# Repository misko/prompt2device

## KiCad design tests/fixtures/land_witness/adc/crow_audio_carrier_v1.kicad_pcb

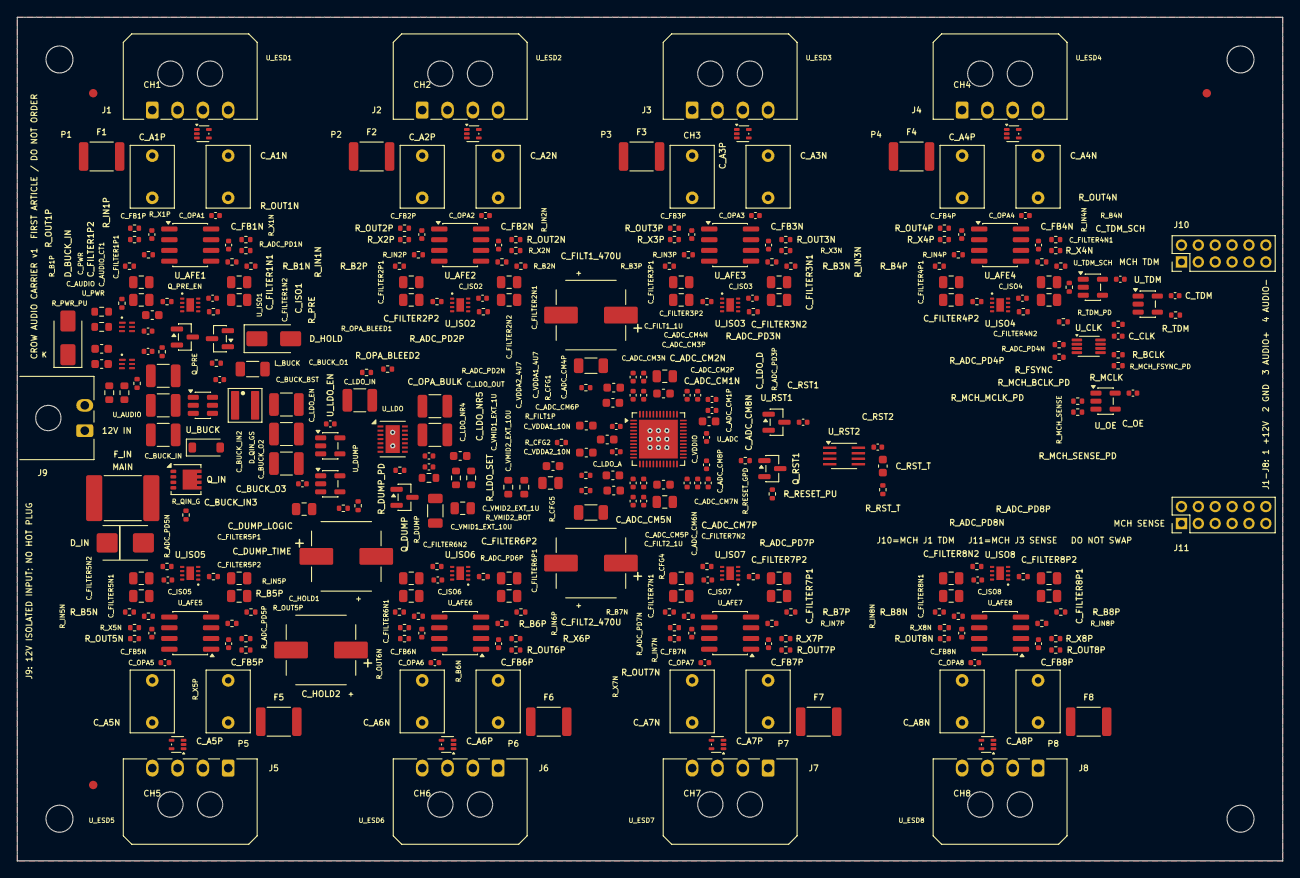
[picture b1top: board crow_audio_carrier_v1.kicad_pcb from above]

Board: 4 copper layers, 150.0 x 100.0 mm, 340 parts (0 on the bottom side), 178 nets, no tracks yet.

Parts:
C_A1N, C_A1P, C_A2N, C_A2P, C_A3N, C_A3P, C_A4N, C_A4P, C_A5N, C_A5P, C_A6N, C_A6P, C_A7N, C_A7P, C_A8N, C_A8P: 1uF; C_Rect_L7.2mm_W5.0mm_P5.00mm
C_ADC_CM1N, C_ADC_CM1P, C_ADC_CM2N, C_ADC_CM2P, C_ADC_CM3N, C_ADC_CM3P, C_ADC_CM4N, C_ADC_CM4P, C_ADC_CM5N, C_ADC_CM5P, C_ADC_CM6N, C_ADC_CM6P, C_ADC_CM7N, C_ADC_CM7P, C_ADC_CM8N, C_ADC_CM8P: 1nF; C_0402_1005Metric
C_AUDIO: 100nF; C_0402_1005Metric
C_AUDIO_CT1, C_AUDIO_CT2: 1uF; C_0603_1608Metric
C_BUCK_BST: 100nF; C_0402_1005Metric
C_BUCK_IN, C_BUCK_IN2, C_BUCK_IN3: 10uF; C_1210_3225Metric
C_BUCK_O1, C_BUCK_O2, C_BUCK_O3: 47uF; C_1210_3225Metric
C_CLK: 100nF; C_0402_1005Metric
C_DUMP_LOGIC: 100nF; C_0402_1005Metric
C_DUMP_TIME: 15nF; C_0805_2012Metric
C_FB1N, C_FB1P, C_FB2N, C_FB2P, C_FB3N, C_FB3P, C_FB4N, C_FB4P, C_FB5N, C_FB5P, C_FB6N, C_FB6P, C_FB7N, C_FB7P, C_FB8N, C_FB8P: 680pF; C_0402_1005Metric
C_FILT1_1U, C_FILT2_1U: 1uF; C_0603_1608Metric
C_FILT1_10U, C_FILT2_10U: 10uF; C_0805_2012Metric
C_FILT1_470U, C_FILT2_470U: 470uF; Panasonic_EEEFK1A471P_8x10.2_Exact
C_FILTER1N1, C_FILTER1N2, C_FILTER1P1, C_FILTER1P2, C_FILTER2N1, C_FILTER2N2, C_FILTER2P1, C_FILTER2P2, C_FILTER3N1, C_FILTER3N2, C_FILTER3P1, C_FILTER3P2, C_FILTER4N1, C_FILTER4N2, C_FILTER4P1, C_FILTER4P2, C_FILTER5N1, C_FILTER5N2, C_FILTER5P1, C_FILTER5P2, C_FILTER6N1, C_FILTER6N2, C_FILTER6P1, C_FILTER6P2, C_FILTER7N1, C_FILTER7N2, C_FILTER7P1, C_FILTER7P2, C_FILTER8N1, C_FILTER8N2, C_FILTER8P1, C_FILTER8P2: 15nF; C_0805_2012Metric
C_HOLD1, C_HOLD2: 470uF; Panasonic_EEEFK1A471P_8x10.2_Exact
C_ISO1, C_ISO2, C_ISO3, C_ISO4, C_ISO5, C_ISO6, C_ISO7, C_ISO8: 100nF; C_0402_1005Metric
C_LDO_A: 4.7uF; C_0603_1608Metric
C_LDO_D: 4.7uF; C_0603_1608Metric
C_LDO_EN: 100nF; C_0402_1005Metric
C_LDO_IN: 47uF; C_1210_3225Metric
C_LDO_NR4, C_LDO_NR5: 1nF; C_0402_1005Metric
C_LDO_OUT: 47uF; C_1210_3225Metric
C_OE: 100nF; C_0402_1005Metric
C_OPA1, C_OPA2, C_OPA3, C_OPA4, C_OPA5, C_OPA6, C_OPA7, C_OPA8: 100nF; C_0402_1005Metric
C_OPA_BULK: 47uF; C_1210_3225Metric
C_PWR: 100nF; C_0402_1005Metric
C_PWR_CT: 1uF; C_0603_1608Metric
C_RST1, C_RST2: 100nF; C_0402_1005Metric
C_RST_T: 220nF; C_0603_1608Metric
C_TDM: 100nF; C_0402_1005Metric
C_TDM_SCH: 100nF; C_0402_1005Metric
C_VDDA1_4U7, C_VDDA2_4U7: 4.7uF; C_0603_1608Metric
C_VDDA1_10N, C_VDDA2_10N: 10nF; C_0402_1005Metric
C_VDDIO: 100nF; C_0402_1005Metric
C_VMID1_4U7, C_VMID2_4U7: 4.7uF; C_0603_1608Metric
C_VMID1_470N, C_VMID2_470N: 470nF; C_0603_1608Metric
C_VMID1_EXT_1U, C_VMID2_EXT_1U: 1uF; C_0603_1608Metric
C_VMID1_EXT_10U, C_VMID2_EXT_10U: 10uF; C_0805_2012Metric
D_BUCK_IN: US1B-13-F; D_SMA
D_HOLD: B340A-13-F; D_SMA
D_IN: SMBJ15A; Littelfuse_SMBJ15A_SMB_Exact
D_QIN_GS: BZT52C12-7-F; D_SOD-123
F1, F2, F3, F4, F5, F6, F7, F8: 1812L035/60MR; Fuse_1812_4532Metric
FID1, FID2, FID3: Fiducial_1mm_Mask2mm
F_IN: 2920L260/33DR; Fuse_2920_7451Metric
H1, H2, H3, H4: MountingHole_3.2mm_M3
J1, J2, J3, J4, J5, J6, J7, J8: 43650-0400; Molex_43650-0400_RA_Exact
J9: 43650-0200; Molex_43650-0200_RA_Exact
J10, J11: TMM-106-01-L-D; Samtec_TMM-106-01-L-D_2x06_P2.00mm_Vertical
L_BUCK: XGL4020-332MEC; Coilcraft_XGL4020_Exact
Q_DUMP: AO3400A; SOT-23
Q_IN: DMP6023LFG-13; Diodes_PowerDI3333-8
Q_PRE: AO3401A; SOT-23
Q_PRE_EN: 2N7002K-7; SOT-23
Q_RST1: 2N7002K-7; SOT-23
R_ADC_BOT: 10kΩ; R_0603_1608Metric
R_ADC_PD1N, R_ADC_PD1P, R_ADC_PD2N, R_ADC_PD2P, R_ADC_PD3N, R_ADC_PD3P, R_ADC_PD4N, R_ADC_PD4P, R_ADC_PD5N, R_ADC_PD5P, R_ADC_PD6N, R_ADC_PD6P, R_ADC_PD7N, R_ADC_PD7P, R_ADC_PD8N, R_ADC_PD8P: 10kΩ; R_0402_1005Metric
R_ADC_TOP: 17.4kΩ; R_0603_1608Metric
R_AUDIO_PD: 100kΩ; R_0402_1005Metric
R_AUDIO_PU: 10kΩ; R_0402_1005Metric
R_B1N, R_B1P, R_B2N, R_B2P, R_B3N, R_B3P, R_B4N, R_B4P, R_B5N, R_B5P, R_B6N, R_B6P, R_B7N, R_B7P, R_B8N, R_B8P: 100kΩ; R_0402_1005Metric
R_BCLK: 22Ω; R_0402_1005Metric
R_CFG1, R_CFG4: 4.7kΩ; R_0402_1005Metric
R_CFG2: 0Ω; R_0402_1005Metric
R_CFG5: 100kΩ; R_0402_1005Metric
R_DUMP: 1Ω; R_1206_3216Metric
R_DUMP_PD: 100kΩ; R_0402_1005Metric
R_DUMP_TIME1, R_DUMP_TIME2: 100kΩ; R_0402_1005Metric
R_FILT1P, R_FILT2P: 1Ω; R_1206_3216Metric
R_FSYNC: 22Ω; R_0402_1005Metric
R_IN1N, R_IN1P, R_IN2N, R_IN2P, R_IN3N, R_IN3P, R_IN4N, R_IN4P, R_IN5N, R_IN5P, R_IN6N, R_IN6P, R_IN7N, R_IN7P, R_IN8N, R_IN8P: 10kΩ; R_0402_1005Metric
R_LDO_SET: 33kΩ; R_0603_1608Metric
R_MCH_BCLK_PD: 10kΩ; R_0402_1005Metric
R_MCH_FSYNC_PD: 10kΩ; R_0402_1005Metric
R_MCH_MCLK_PD: 10kΩ; R_0402_1005Metric
R_MCH_SENSE: 300Ω; R_0402_1005Metric
R_MCH_SENSE_PD: 10kΩ; R_0402_1005Metric
R_MCLK: 22Ω; R_0402_1005Metric
R_OPA_BLEED1, R_OPA_BLEED2: 100Ω; R_0402_1005Metric
R_OUT1N, R_OUT1P, R_OUT2N, R_OUT2P, R_OUT3N, R_OUT3P, R_OUT4N, R_OUT4P, R_OUT5N, R_OUT5P, R_OUT6N, R_OUT6P, R_OUT7N, R_OUT7P, R_OUT8N, R_OUT8P: 10Ω; R_0402_1005Metric
R_PRE: 22Ω; R_1206_3216Metric
R_PRE_G: 100kΩ; R_0402_1005Metric
R_PWR_BOT: 10kΩ; R_0603_1608Metric
R_PWR_PU: 10kΩ; R_0402_1005Metric
R_PWR_TOP: 30.9kΩ; R_0603_1608Metric
R_QIN_G: 100kΩ; R_0402_1005Metric
R_RESET_GPD: 100kΩ; R_0402_1005Metric
R_RESET_PU: 10kΩ; R_0402_1005Metric
R_RST_T: 100kΩ; R_0402_1005Metric
R_TDM: 33Ω; R_0402_1005Metric
R_TDM_PD: 10kΩ; R_0402_1005Metric
R_VMID1_BOT, R_VMID1_TOP, R_VMID2_BOT, R_VMID2_TOP: 1kΩ; R_0603_1608Metric
R_X1N, R_X1P, R_X2N, R_X2P, R_X3N, R_X3P, R_X4N, R_X4P, R_X5N, R_X5P, R_X6N, R_X6P, R_X7N, R_X7P, R_X8N, R_X8P: 300Ω; R_0402_1005Metric
U_ADC: CS5308P-DN; Cirrus_CS5308P_QFN48_6x6_P0.4_EP4.6
U_AFE1, U_AFE2, U_AFE3, U_AFE4, U_AFE5, U_AFE6, U_AFE7, U_AFE8: OPA2320AIDR; SOIC-8_3.9x4.9mm_P1.27mm
U_AUDIO: TPS389001DSER; TI_DSE0006A_Exact
U_BUCK: AP63205WU-7; TSOT-23-6
U_CLK: SN74LVC3G34DCUR; VSSOP-8_2.3x2mm_P0.5mm
U_DUMP: 74LVC1G14GV,125; SOT-23-5
U_ESD1, U_ESD2, U_ESD3, U_ESD4, U_ESD5, U_ESD6, U_ESD7, U_ESD8: TPD2E2U06DRLR; SOT-553
U_ISO1, U_ISO2, U_ISO3, U_ISO4, U_ISO5, U_ISO6, U_ISO7, U_ISO8: TMUX2821DSGR; TI_DSG0008A_Exact
U_LDO: LT3041ADE#TRPBF; DFN-14-1EP_3x4mm_P0.5mm_EP1.7x3.3mm
U_LDO_EN: 74LVC1G14GV,125; SOT-23-5
U_OE: 74LVC1G14GV,125; SOT-23-5
U_PWR: TPS389001DSER; TI_DSE0006A_Exact
U_RST1: TPS3839K33DBZR; SOT-23
U_RST2: SN74LVC1G123DCTR; SSOP-8_2.95x2.8mm_P0.65mm
U_TDM: SN74LVC1G125DBVR; SOT-23-5
U_TDM_SCH: 74LVC1G17GV,125; SOT-23-5

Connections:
3V3_ADC: C_CLK.1, C_LDO_OUT.1, C_OE.1, C_OPA1.1, C_OPA2.1, C_OPA3.1, C_OPA4.1, C_OPA5.1, C_OPA6.1, C_OPA7.1, C_OPA8.1, C_OPA_BULK.1, C_RST1.1, C_RST2.1, C_TDM.1, C_TDM_SCH.1, C_VDDA1_4U7.1, C_VDDA1_10N.1, C_VDDA2_4U7.1, C_VDDA2_10N.1, C_VDDIO.1, R_ADC_TOP.1, R_CFG2.2, R_CFG4.2, R_DUMP.1, R_FILT1P.1, R_FILT2P.1, R_OPA_BLEED1.1, R_RESET_PU.1, R_RST_T.1, R_VMID1_TOP.1, R_VMID2_TOP.1, U_ADC.5, U_ADC.9, U_ADC.31, U_ADC.38, U_AFE1.8, U_AFE2.8, U_AFE3.8, U_AFE4.8, U_AFE5.8, U_AFE6.8, U_AFE7.8, U_AFE8.8, U_CLK.8, U_LDO.12, U_LDO.13, U_LDO.14, U_OE.5, U_RST1.3, U_RST2.2, U_RST2.8, U_TDM.5, U_TDM_SCH.5
5V_BUCK: C_BUCK_O1.1, C_BUCK_O2.1, C_BUCK_O3.1, D_HOLD.2, L_BUCK.2, R_PWR_TOP.1, U_BUCK.1
5V_LDO_FEED: D_HOLD.1, Q_PRE.2, R_PRE.1, R_PRE_G.2
5V_LDO_HOLD: C_AUDIO.1, C_DUMP_LOGIC.1, C_HOLD1.1, C_HOLD2.1, C_ISO1.1, C_ISO2.1, C_ISO3.1, C_ISO4.1, C_ISO5.1, C_ISO6.1, C_ISO7.1, C_ISO8.1, C_LDO_EN.1, C_LDO_IN.1, C_PWR.1, Q_PRE.3, R_AUDIO_PU.1, R_PRE.2, R_PWR_PU.1, U_AUDIO.4, U_DUMP.5, U_ISO1.8, U_ISO2.8, U_ISO3.8, U_ISO4.8, U_ISO5.8, U_ISO6.8, U_ISO7.8, U_ISO8.8, U_LDO.1, U_LDO.2, U_LDO.3, U_LDO.8, U_LDO_EN.5, U_PWR.3, U_PWR.4
12V_BUCK_IN: C_BUCK_IN.1, C_BUCK_IN2.1, C_BUCK_IN3.1, D_BUCK_IN.1, U_BUCK.2, U_BUCK.3
12V_FUSED: F_IN.2, Q_IN.5
12V_IN: F_IN.1, J9.1
12V_POD1: F1.2, J1.1
12V_POD2: F2.2, J2.1
12V_POD3: F3.2, J3.1
12V_POD4: F4.2, J4.1
12V_POD5: F5.2, J5.1
12V_POD6: F6.2, J6.1
12V_POD7: F7.2, J7.1
12V_POD8: F8.2, J8.1
12V_PROTECTED: D_BUCK_IN.2, D_IN.1, D_QIN_GS.1, F1.1, F2.1, F3.1, F4.1, F5.1, F6.1, F7.1, F8.1, Q_IN.1, Q_IN.2, Q_IN.3
ADC1N: C_ADC_CM1N.1, R_ADC_PD1N.1, U_ADC.39, U_ISO1.6
ADC1P: C_ADC_CM1P.1, R_ADC_PD1P.1, U_ADC.40, U_ISO1.2
ADC2N: C_ADC_CM2N.1, R_ADC_PD2N.1, U_ADC.41, U_ISO2.6
ADC2P: C_ADC_CM2P.1, R_ADC_PD2P.1, U_ADC.42, U_ISO2.2
ADC3N: C_ADC_CM3N.1, R_ADC_PD3N.1, U_ADC.45, U_ISO3.6
ADC3P: C_ADC_CM3P.1, R_ADC_PD3P.1, U_ADC.46, U_ISO3.2
ADC4N: C_ADC_CM4N.1, R_ADC_PD4N.1, U_ADC.47, U_ISO4.6
ADC4P: C_ADC_CM4P.1, R_ADC_PD4P.1, U_ADC.48, U_ISO4.2
ADC5N: C_ADC_CM5N.1, R_ADC_PD5N.1, U_ADC.13, U_ISO5.6
ADC5P: C_ADC_CM5P.1, R_ADC_PD5P.1, U_ADC.14, U_ISO5.2
ADC6N: C_ADC_CM6N.1, R_ADC_PD6N.1, U_ADC.15, U_ISO6.6
ADC6P: C_ADC_CM6P.1, R_ADC_PD6P.1, U_ADC.16, U_ISO6.2
ADC7N: C_ADC_CM7N.1, R_ADC_PD7N.1, U_ADC.19, U_ISO7.6
ADC7P: C_ADC_CM7P.1, R_ADC_PD7P.1, U_ADC.20, U_ISO7.2
ADC8N: C_ADC_CM8N.1, R_ADC_PD8N.1, U_ADC.21, U_ISO8.6
ADC8P: C_ADC_CM8P.1, R_ADC_PD8P.1, U_ADC.22, U_ISO8.2
ADC_BCLK: R_BCLK.2, U_ADC.29
ADC_DUMP: Q_DUMP.3, R_DUMP.2
ADC_FSYNC: R_FSYNC.2, U_ADC.24
ADC_MCLK: R_MCLK.2, U_ADC.34
ADC_RESET_N: Q_RST1.3, R_RESET_PU.2, U_ADC.23
ADC_SENSE: R_ADC_BOT.1, R_ADC_TOP.2, U_AUDIO.1
ADC_TDM: J10.2, R_TDM.2
AIN_N1: R_IN1N.2, U_AFE1.5
AIN_N2: R_IN2N.2, U_AFE2.5
AIN_N3: R_IN3N.2, U_AFE3.5
AIN_N4: R_IN4N.2, U_AFE4.5
AIN_N5: R_IN5N.2, U_AFE5.5
AIN_N6: R_IN6N.2, U_AFE6.5
AIN_N7: R_IN7N.2, U_AFE7.5
AIN_N8: R_IN8N.2, U_AFE8.5
AIN_P1: R_IN1P.2, U_AFE1.3
AIN_P2: R_IN2P.2, U_AFE2.3
AIN_P3: R_IN3P.2, U_AFE3.3
AIN_P4: R_IN4P.2, U_AFE4.3
AIN_P5: R_IN5P.2, U_AFE5.3
AIN_P6: R_IN6P.2, U_AFE6.3
AIN_P7: R_IN7P.2, U_AFE7.3
AIN_P8: R_IN8P.2, U_AFE8.3
AUDIO_CT: C_AUDIO_CT1.1, C_AUDIO_CT2.1, U_AUDIO.5
AUDIO_EN: R_AUDIO_PD.1, R_AUDIO_PU.2, U_AUDIO.6, U_ISO1.3, U_ISO1.7, U_ISO2.3, U_ISO2.7, U_ISO3.3, U_ISO3.7, U_ISO4.3, U_ISO4.7, U_ISO5.3, U_ISO5.7, U_ISO6.3, U_ISO6.7, U_ISO7.3, U_ISO7.7, U_ISO8.3, U_ISO8.7
AUDIO_N1: C_A1N.1, J1.4, U_ESD1.5
AUDIO_N2: C_A2N.1, J2.4, U_ESD2.5
AUDIO_N3: C_A3N.1, J3.4, U_ESD3.5
AUDIO_N4: C_A4N.1, J4.4, U_ESD4.5
AUDIO_N5: C_A5N.1, J5.4, U_ESD5.5
AUDIO_N6: C_A6N.1, J6.4, U_ESD6.5
AUDIO_N7: C_A7N.1, J7.4, U_ESD7.5
AUDIO_N8: C_A8N.1, J8.4, U_ESD8.5
AUDIO_P1: C_A1P.1, J1.3, U_ESD1.3
AUDIO_P2: C_A2P.1, J2.3, U_ESD2.3
AUDIO_P3: C_A3P.1, J3.3, U_ESD3.3
AUDIO_P4: C_A4P.1, J4.3, U_ESD4.3
AUDIO_P5: C_A5P.1, J5.3, U_ESD5.3
AUDIO_P6: C_A6P.1, J6.3, U_ESD6.3
AUDIO_P7: C_A7P.1, J7.3, U_ESD7.3
AUDIO_P8: C_A8P.1, J8.3, U_ESD8.3
BCLK_BUF: R_BCLK.1, U_CLK.5
BIAS_N1: C_A1N.2, R_B1N.1, R_IN1N.1
BIAS_N2: C_A2N.2, R_B2N.1, R_IN2N.1
BIAS_N3: C_A3N.2, R_B3N.1, R_IN3N.1
BIAS_N4: C_A4N.2, R_B4N.1, R_IN4N.1
BIAS_N5: C_A5N.2, R_B5N.1, R_IN5N.1
BIAS_N6: C_A6N.2, R_B6N.1, R_IN6N.1
BIAS_N7: C_A7N.2, R_B7N.1, R_IN7N.1
BIAS_N8: C_A8N.2, R_B8N.1, R_IN8N.1
BIAS_P1: C_A1P.2, R_B1P.1, R_IN1P.1
BIAS_P2: C_A2P.2, R_B2P.1, R_IN2P.1
BIAS_P3: C_A3P.2, R_B3P.1, R_IN3P.1
BIAS_P4: C_A4P.2, R_B4P.1, R_IN4P.1
BIAS_P5: C_A5P.2, R_B5P.1, R_IN5P.1
BIAS_P6: C_A6P.2, R_B6P.1, R_IN6P.1
BIAS_P7: C_A7P.2, R_B7P.1, R_IN7P.1
BIAS_P8: C_A8P.2, R_B8P.1, R_IN8P.1
BUCK_BST: C_BUCK_BST.1, U_BUCK.6
BUCK_SW: C_BUCK_BST.2, L_BUCK.1, U_BUCK.5
CFG1: R_CFG1.1, U_ADC.2
CFG2: R_CFG2.1, U_ADC.3
CFG4: R_CFG4.1, U_ADC.10
CFG5: R_CFG5.1, U_ADC.11
DUMP_GATE: Q_DUMP.1, R_DUMP_PD.1, U_DUMP.4, U_LDO_EN.2
DUMP_RC: C_DUMP_TIME.1, R_DUMP_TIME1.2, R_DUMP_TIME2.2, U_DUMP.2
FB_N1: C_FB1N.1, R_X1N.1, U_AFE1.6
FB_N2: C_FB2N.1, R_X2N.1, U_AFE2.6
FB_N3: C_FB3N.1, R_X3N.1, U_AFE3.6
FB_N4: C_FB4N.1, R_X4N.1, U_AFE4.6
FB_N5: C_FB5N.1, R_X5N.1, U_AFE5.6
FB_N6: C_FB6N.1, R_X6N.1, U_AFE6.6
FB_N7: C_FB7N.1, R_X7N.1, U_AFE7.6
FB_N8: C_FB8N.1, R_X8N.1, U_AFE8.6
FB_P1: C_FB1P.1, R_X1P.1, U_AFE1.2
FB_P2: C_FB2P.1, R_X2P.1, U_AFE2.2
FB_P3: C_FB3P.1, R_X3P.1, U_AFE3.2
FB_P4: C_FB4P.1, R_X4P.1, U_AFE4.2
FB_P5: C_FB5P.1, R_X5P.1, U_AFE5.2
FB_P6: C_FB6P.1, R_X6P.1, U_AFE6.2
FB_P7: C_FB7P.1, R_X7P.1, U_AFE7.2
FB_P8: C_FB8P.1, R_X8P.1, U_AFE8.2
FILT1P: C_FILT1_1U.1, C_FILT1_10U.1, C_FILT1_470U.1, R_FILT1P.2, U_ADC.43
FILT2P: C_FILT2_1U.1, C_FILT2_10U.1, C_FILT2_470U.1, R_FILT2P.2, U_ADC.18
FILTER1N: C_FILTER1N1.1, C_FILTER1N2.1, R_OUT1N.2, R_X1N.2, U_ISO1.5
FILTER1P: C_FILTER1P1.1, C_FILTER1P2.1, R_OUT1P.2, R_X1P.2, U_ISO1.1
FILTER2N: C_FILTER2N1.1, C_FILTER2N2.1, R_OUT2N.2, R_X2N.2, U_ISO2.5
FILTER2P: C_FILTER2P1.1, C_FILTER2P2.1, R_OUT2P.2, R_X2P.2, U_ISO2.1
FILTER3N: C_FILTER3N1.1, C_FILTER3N2.1, R_OUT3N.2, R_X3N.2, U_ISO3.5
FILTER3P: C_FILTER3P1.1, C_FILTER3P2.1, R_OUT3P.2, R_X3P.2, U_ISO3.1
FILTER4N: C_FILTER4N1.1, C_FILTER4N2.1, R_OUT4N.2, R_X4N.2, U_ISO4.5
FILTER4P: C_FILTER4P1.1, C_FILTER4P2.1, R_OUT4P.2, R_X4P.2, U_ISO4.1
FILTER5N: C_FILTER5N1.1, C_FILTER5N2.1, R_OUT5N.2, R_X5N.2, U_ISO5.5
FILTER5P: C_FILTER5P1.1, C_FILTER5P2.1, R_OUT5P.2, R_X5P.2, U_ISO5.1
FILTER6N: C_FILTER6N1.1, C_FILTER6N2.1, R_OUT6N.2, R_X6N.2, U_ISO6.5
FILTER6P: C_FILTER6P1.1, C_FILTER6P2.1, R_OUT6P.2, R_X6P.2, U_ISO6.1
FILTER7N: C_FILTER7N1.1, C_FILTER7N2.1, R_OUT7N.2, R_X7N.2, U_ISO7.5
FILTER7P: C_FILTER7P1.1, C_FILTER7P2.1, R_OUT7P.2, R_X7P.2, U_ISO7.1
FILTER8N: C_FILTER8N1.1, C_FILTER8N2.1, R_OUT8N.2, R_X8N.2, U_ISO8.5
FILTER8P: C_FILTER8P1.1, C_FILTER8P2.1, R_OUT8P.2, R_X8P.2, U_ISO8.1
FSYNC_BUF: R_FSYNC.1, U_CLK.2
GND: C_ADC_CM1N.2, C_ADC_CM1P.2, C_ADC_CM2N.2, C_ADC_CM2P.2, C_ADC_CM3N.2, C_ADC_CM3P.2, C_ADC_CM4N.2, C_ADC_CM4P.2, C_ADC_CM5N.2, C_ADC_CM5P.2, C_ADC_CM6N.2, C_ADC_CM6P.2, C_ADC_CM7N.2, C_ADC_CM7P.2, C_ADC_CM8N.2, C_ADC_CM8P.2, C_AUDIO.2, C_AUDIO_CT1.2, C_AUDIO_CT2.2, C_BUCK_IN.2, C_BUCK_IN2.2, C_BUCK_IN3.2, C_BUCK_O1.2, C_BUCK_O2.2, C_BUCK_O3.2, C_CLK.2, C_DUMP_LOGIC.2, C_DUMP_TIME.2, C_FILT1_1U.2, C_FILT1_10U.2, C_FILT1_470U.2, C_FILT2_1U.2, C_FILT2_10U.2, C_FILT2_470U.2, C_FILTER1N1.2, C_FILTER1N2.2, C_FILTER1P1.2, C_FILTER1P2.2, C_FILTER2N1.2, C_FILTER2N2.2, C_FILTER2P1.2, C_FILTER2P2.2, C_FILTER3N1.2, C_FILTER3N2.2, C_FILTER3P1.2, C_FILTER3P2.2, C_FILTER4N1.2, C_FILTER4N2.2, C_FILTER4P1.2, C_FILTER4P2.2, C_FILTER5N1.2, C_FILTER5N2.2, C_FILTER5P1.2, C_FILTER5P2.2, C_FILTER6N1.2, C_FILTER6N2.2, C_FILTER6P1.2, C_FILTER6P2.2, C_FILTER7N1.2, C_FILTER7N2.2, C_FILTER7P1.2, C_FILTER7P2.2, C_FILTER8N1.2, C_FILTER8N2.2, C_FILTER8P1.2, C_FILTER8P2.2, C_HOLD1.2, C_HOLD2.2, C_ISO1.2, C_ISO2.2, C_ISO3.2, C_ISO4.2, C_ISO5.2, C_ISO6.2, C_ISO7.2, C_ISO8.2, C_LDO_A.2, C_LDO_D.2, C_LDO_EN.2, C_LDO_IN.2, C_LDO_NR4.2, C_LDO_NR5.2, C_LDO_OUT.2, C_OE.2, C_OPA1.2, C_OPA2.2, C_OPA3.2, C_OPA4.2, C_OPA5.2, C_OPA6.2, C_OPA7.2, C_OPA8.2, C_OPA_BULK.2, C_PWR.2, C_PWR_CT.2, C_RST1.2, C_RST2.2, C_TDM.2, C_TDM_SCH.2, C_VDDA1_4U7.2, C_VDDA1_10N.2, C_VDDA2_4U7.2, C_VDDA2_10N.2, C_VDDIO.2, C_VMID1_4U7.2, C_VMID1_470N.2, C_VMID1_EXT_1U.2, C_VMID1_EXT_10U.2, C_VMID2_4U7.2, C_VMID2_470N.2, C_VMID2_EXT_1U.2, C_VMID2_EXT_10U.2, D_IN.2, J1.2, J2.2, J3.2, J4.2, J5.2, J6.2, J7.2, J8.2, J9.2, J10.11, J11.1, Q_DUMP.2, Q_PRE_EN.2, Q_RST1.2, R_ADC_BOT.2, R_ADC_PD1N.2, R_ADC_PD1P.2, R_ADC_PD2N.2, R_ADC_PD2P.2, R_ADC_PD3N.2, R_ADC_PD3P.2, R_ADC_PD4N.2, R_ADC_PD4P.2, R_ADC_PD5N.2, R_ADC_PD5P.2, R_ADC_PD6N.2, R_ADC_PD6P.2, R_ADC_PD7N.2, R_ADC_PD7P.2, R_ADC_PD8N.2, R_ADC_PD8P.2, R_AUDIO_PD.2, R_CFG1.2, R_CFG5.2, R_DUMP_PD.2, R_LDO_SET.2, R_MCH_BCLK_PD.2, R_MCH_FSYNC_PD.2, R_MCH_MCLK_PD.2, R_MCH_SENSE_PD.2, R_OPA_BLEED2.2, R_PWR_BOT.2, R_QIN_G.2, R_RESET_GPD.2, R_TDM_PD.2, R_VMID1_BOT.2, R_VMID2_BOT.2, U_ADC.4, U_ADC.6, U_ADC.8, U_ADC.17, U_ADC.30, U_ADC.35, U_ADC.36, U_ADC.37, U_ADC.44, U_ADC.49, U_AFE1.4, U_AFE2.4, U_AFE3.4, U_AFE4.4, U_AFE5.4, U_AFE6.4, U_AFE7.4, U_AFE8.4, U_AUDIO.2, U_BUCK.4, U_CLK.4, U_DUMP.3, U_ESD1.4, U_ESD2.4, U_ESD3.4, U_ESD4.4, U_ESD5.4, U_ESD6.4, U_ESD7.4, U_ESD8.4, U_ISO1.4, U_ISO1.9, U_ISO2.4, U_ISO2.9, U_ISO3.4, U_ISO3.9, U_ISO4.4, U_ISO4.9, U_ISO5.4, U_ISO5.9, U_ISO6.4, U_ISO6.9, U_ISO7.4, U_ISO7.9, U_ISO8.4, U_ISO8.9, U_LDO.7, U_LDO.10, U_LDO.11, U_LDO.15, U_LDO_EN.3, U_OE.3, U_PWR.2, U_RST1.1, U_RST2.1, U_RST2.4, U_TDM.3, U_TDM_SCH.3
LDO_A_FILT: C_LDO_A.1, U_ADC.7
LDO_D_FILT: C_LDO_D.1, U_ADC.32, U_ADC.33
LDO_EN: U_LDO.5, U_LDO_EN.4
LDO_NR: C_LDO_NR4.1, C_LDO_NR5.1, R_LDO_SET.1, U_LDO.9
MCH_3V3_SENSE: J11.2, R_MCH_SENSE.1
MCH_BCLK: J10.10, R_MCH_BCLK_PD.1, U_CLK.3
MCH_FSYNC: J10.12, R_MCH_FSYNC_PD.1, U_CLK.6
MCH_MCLK: J10.9, R_MCH_MCLK_PD.1, U_CLK.1
MCLK_BUF: R_MCLK.1, U_CLK.7
OPA_BLEED_A: R_OPA_BLEED1.2, R_OPA_BLEED2.1
OPA_N1: C_FB1N.2, R_OUT1N.1, U_AFE1.7
OPA_N2: C_FB2N.2, R_OUT2N.1, U_AFE2.7
OPA_N3: C_FB3N.2, R_OUT3N.1, U_AFE3.7
OPA_N4: C_FB4N.2, R_OUT4N.1, U_AFE4.7
OPA_N5: C_FB5N.2, R_OUT5N.1, U_AFE5.7
OPA_N6: C_FB6N.2, R_OUT6N.1, U_AFE6.7
OPA_N7: C_FB7N.2, R_OUT7N.1, U_AFE7.7
OPA_N8: C_FB8N.2, R_OUT8N.1, U_AFE8.7
OPA_P1: C_FB1P.2, R_OUT1P.1, U_AFE1.1
OPA_P2: C_FB2P.2, R_OUT2P.1, U_AFE2.1
OPA_P3: C_FB3P.2, R_OUT3P.1, U_AFE3.1
OPA_P4: C_FB4P.2, R_OUT4P.1, U_AFE4.1
OPA_P5: C_FB5P.2, R_OUT5P.1, U_AFE5.1
OPA_P6: C_FB6P.2, R_OUT6P.1, U_AFE6.1
OPA_P7: C_FB7P.2, R_OUT7P.1, U_AFE7.1
OPA_P8: C_FB8P.2, R_OUT8P.1, U_AFE8.1
POR_N: U_RST1.2, U_RST2.3
PRE_GATE: Q_PRE.1, Q_PRE_EN.3, R_PRE_G.1
PWR_CT: C_PWR_CT.1, U_PWR.5
PWR_EN: Q_PRE_EN.1, R_DUMP_TIME1.1, R_DUMP_TIME2.1, R_PWR_PU.2, U_AUDIO.3, U_PWR.6
PWR_SENSE: R_PWR_BOT.1, R_PWR_TOP.2, U_PWR.1
Q_IN_GATE: D_QIN_GS.2, Q_IN.4, R_QIN_G.1
RESET_C: C_RST_T.1, U_RST2.6
RESET_PULSE_H: Q_RST1.1, R_RESET_GPD.1, U_RST2.5
RESET_RC: C_RST_T.2, R_RST_T.2, U_RST2.7
TDM_BUFFERED: R_TDM.1, U_TDM.4
TDM_CLEAN: U_TDM.2, U_TDM_SCH.4
TDM_OE_N: U_OE.4, U_TDM.1
TDM_RAW: R_TDM_PD.1, U_ADC.25, U_TDM_SCH.2
TDM_SENSE_G: R_MCH_SENSE.2, R_MCH_SENSE_PD.1, U_OE.2
VMID1: C_VMID1_4U7.1, C_VMID1_470N.1, U_ADC.1
VMID1_EXT: C_VMID1_EXT_1U.1, C_VMID1_EXT_10U.1, R_B1N.2, R_B1P.2, R_B2N.2, R_B2P.2, R_B3N.2, R_B3P.2, R_B4N.2, R_B4P.2, R_VMID1_BOT.1, R_VMID1_TOP.2
VMID2: C_VMID2_4U7.1, C_VMID2_470N.1, U_ADC.12
VMID2_EXT: C_VMID2_EXT_1U.1, C_VMID2_EXT_10U.1, R_B5N.2, R_B5P.2, R_B6N.2, R_B6P.2, R_B7N.2, R_B7P.2, R_B8N.2, R_B8P.2, R_VMID2_BOT.1, R_VMID2_TOP.2

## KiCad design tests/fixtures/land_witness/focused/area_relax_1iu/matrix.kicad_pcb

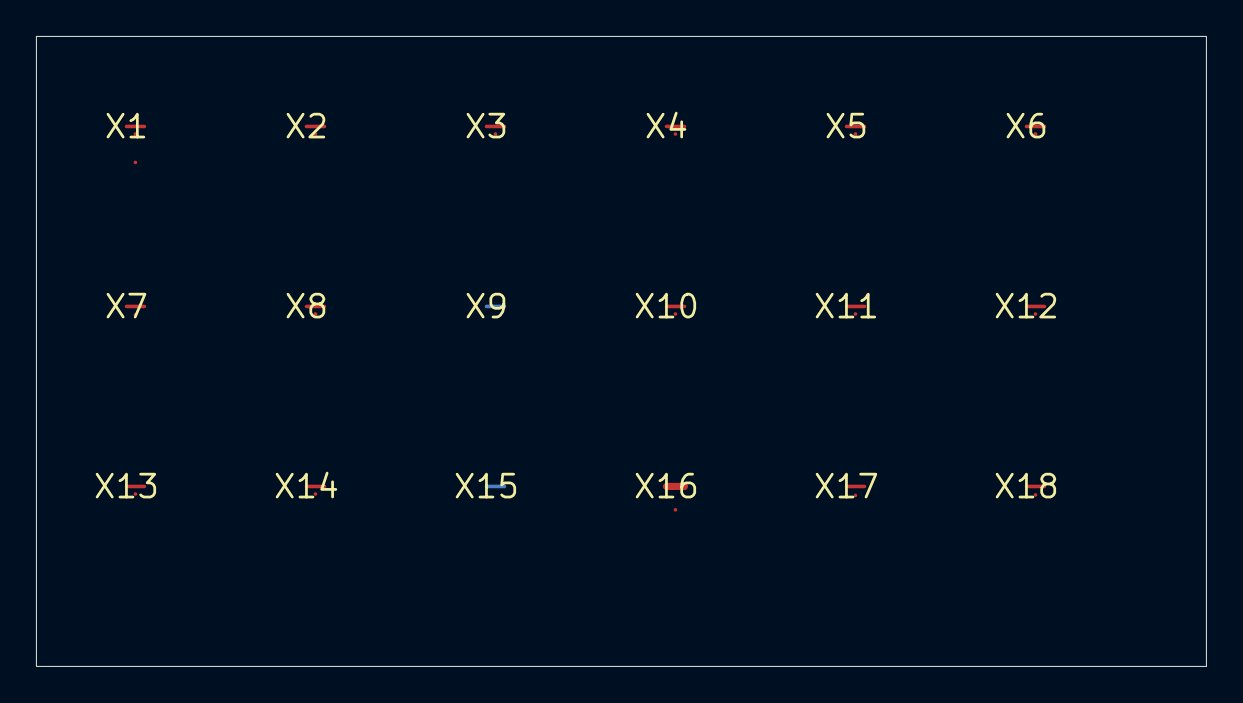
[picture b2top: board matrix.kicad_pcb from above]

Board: 2 copper layers, 65.0 x 35.0 mm, 18 parts (0 on the bottom side), 18 nets.

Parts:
X1: remote_high
X2: b_side
X3: reversal
X4: both_area
X5: offcenter
X6: contained
X7: padpad_guard
X8: track_width
X9: area_layer
X10: last_match
X11: boolean_left
X12: negation
X13: wildcard
X14: multi_constraint
X15: rule_layer
X16: width_transition
X17: oscillation
X18: one_sided

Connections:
area_layer_T: X9.1, X9.2
b_side_T: X2.1, X2.2
boolean_left_T: X11.1, X11.2
both_area_T: X4.1, X4.2
contained_T: X6.1, X6.2
last_match_T: X10.1, X10.2
multi_constraint_T: X14.1, X14.2
negation_T: X12.1, X12.2
offcenter_T: X5.1, X5.2
one_sided_T: X18.1, X18.2
oscillation_T: X17.1, X17.2
padpad_guard_T: X7.1, X7.2
remote_high_T: X1.1, X1.2
reversal_T: X3.1, X3.2
rule_layer_T: X15.1, X15.2
track_width_T: X8.1, X8.2
width_transition_T: X16.1, X16.2
wildcard_T: X13.1, X13.2
